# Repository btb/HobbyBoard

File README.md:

# HobbyBoard

## Reproduction of the original Apple Hobby/Prototyping Board

## Miniaturized version

Download gerber files at https://github.com/btb/HobbyBoard/releases

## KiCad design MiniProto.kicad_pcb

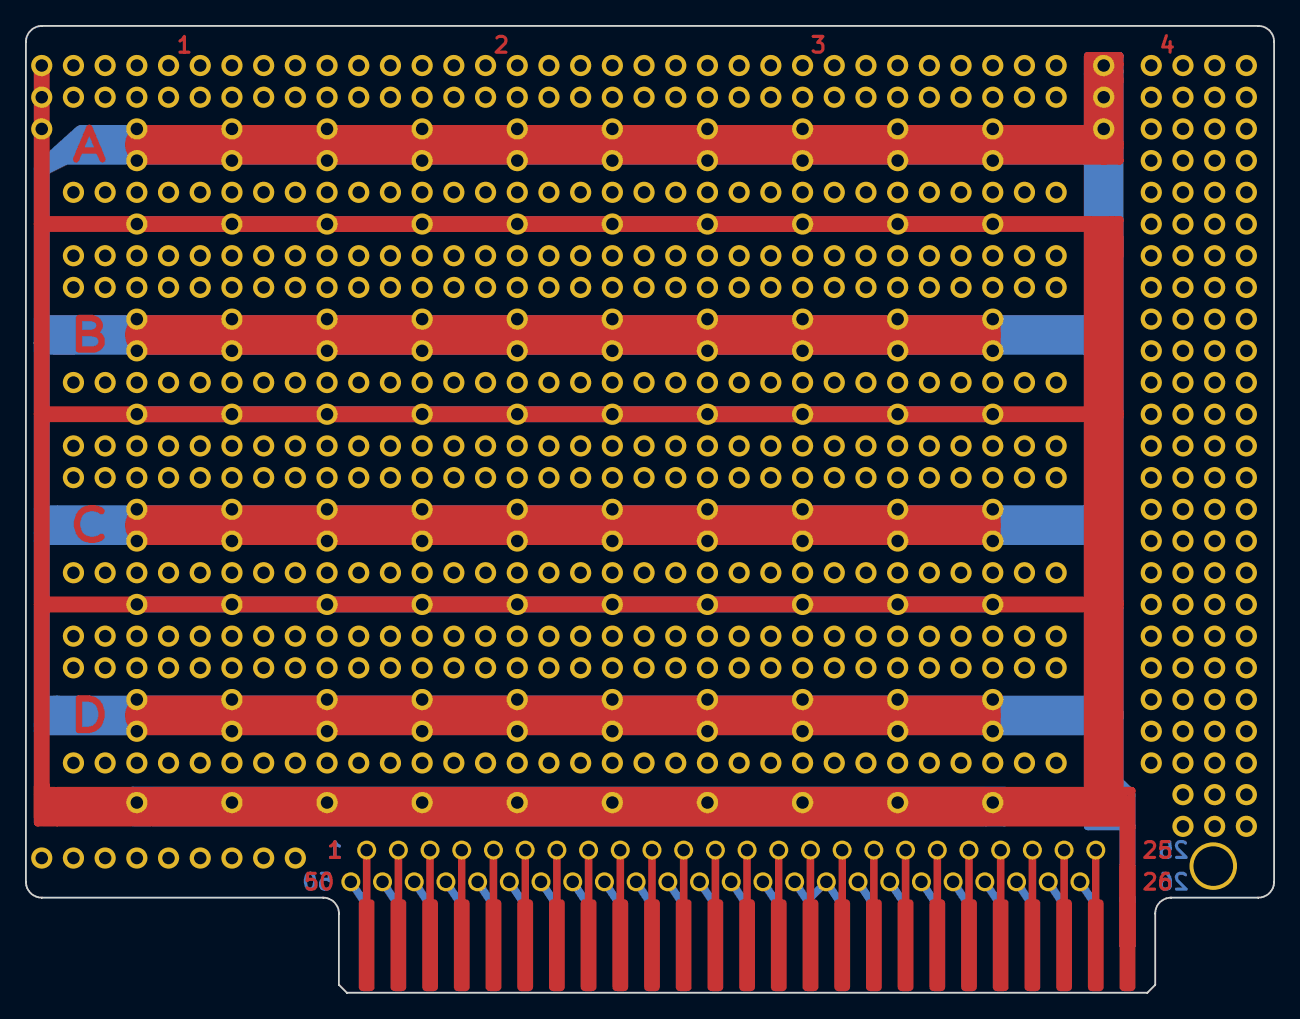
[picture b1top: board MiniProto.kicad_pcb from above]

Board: 2 copper layers, 100.0 x 77.5 mm, 4 parts (0 on the bottom side), 16 nets.

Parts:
H2: .125_Mounting_Hole; PTH_.125_ID
J1: Apple II Expansion Bus; Apple II Expansion Edge Connector
J2: Back Side; PinHeader_1x24_P2.54mm_Vertical
J3: Front Side; PinHeader_1x24_P2.54mm_Vertical

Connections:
unnamed: J1.1 (~IO_SELECT), J3.1
unnamed: J1.19 (N.C.), J3.19
unnamed: J1.20 (~I/O_STROBE), J3.20
unnamed: J1.21 (RDY), J3.21
unnamed: J1.22 (~DMA), J3.22
unnamed: J1.29 (~NMI), J2.3
unnamed: J1.30 (~IRQ), J2.4
unnamed: J1.31 (~RES), J2.5
unnamed: J1.33 (-12V), J2.7
unnamed: J1.34 (-5V), J2.8
unnamed: J1.35 (N.C.), J2.9
unnamed: J1.36 (7M), J2.10
unnamed: J1.37 (Q3), J2.11
unnamed: J1.38 (PHI1), J2.12
unnamed: J1.39 (USER1), J2.13
unnamed: J1.50 (-12V), J2.24

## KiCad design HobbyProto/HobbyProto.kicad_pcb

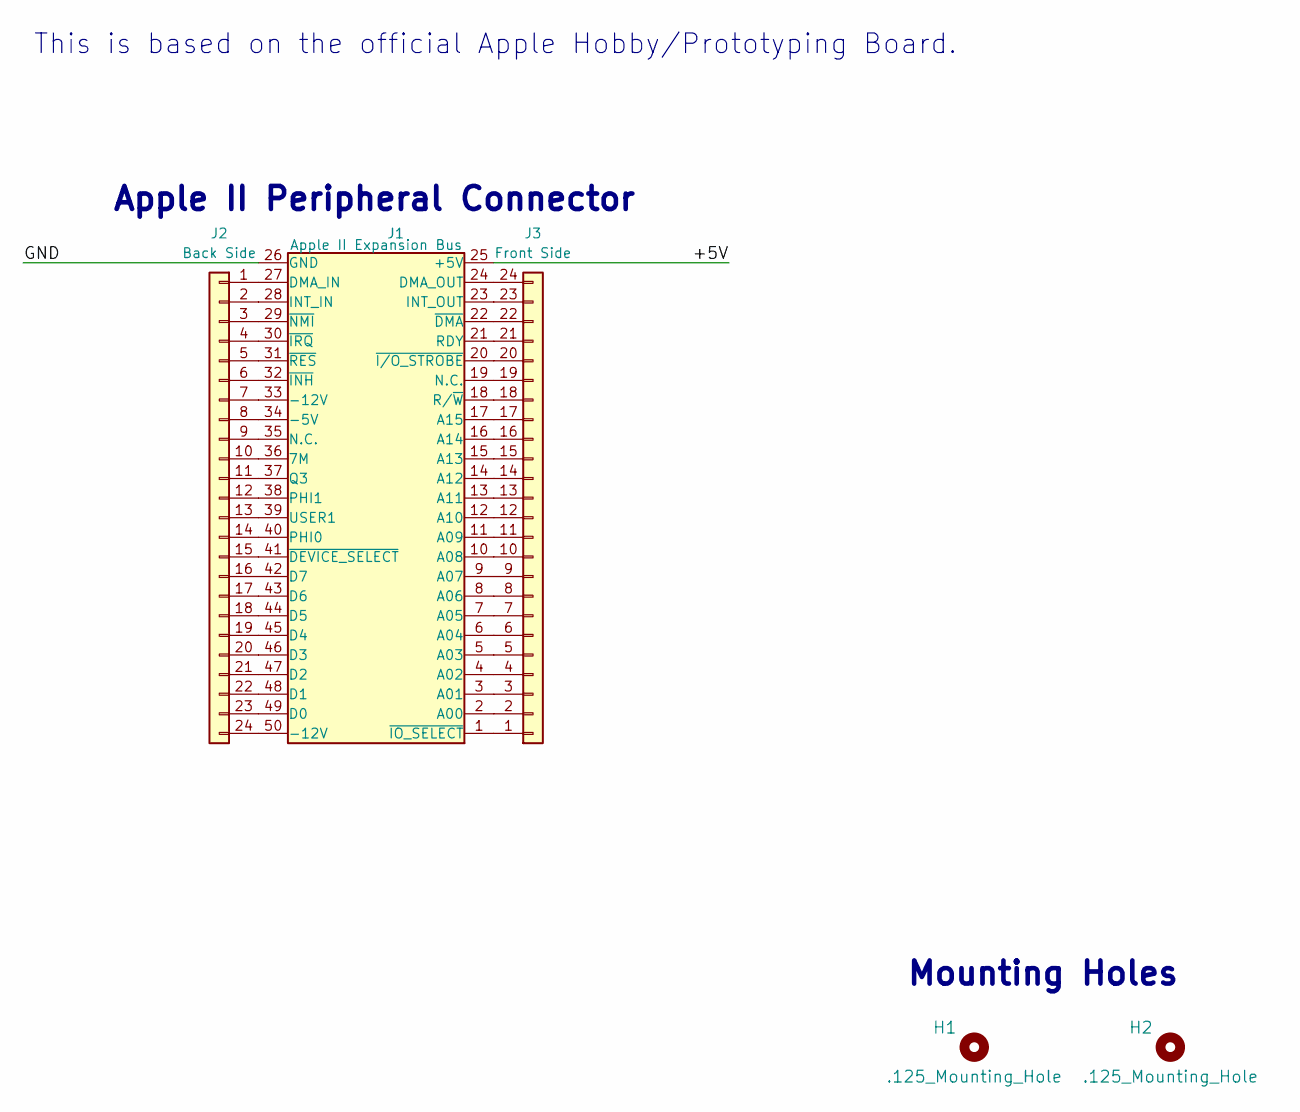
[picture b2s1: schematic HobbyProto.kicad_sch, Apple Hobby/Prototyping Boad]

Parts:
H1: .125_Mounting_Hole; NPTH_3mm_ID
H2: .125_Mounting_Hole; PTH_.125_ID
J1: Apple II Expansion Bus; Apple II Expansion Edge Connector
J2: Back Side; PinHeader_1x24_P2.54mm_Vertical
J3: Front Side; PinHeader_1x24_P2.54mm_Vertical

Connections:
/+5V: J1.25 (+5V)
/GND: J1.26 (GND)
unnamed: J1.1 (~IO_SELECT), J3.1
unnamed: J1.2 (A00), J3.2
unnamed: J1.3 (A01), J3.3
unnamed: J1.4 (A02), J3.4
unnamed: J1.5 (A03), J3.5
unnamed: J1.6 (A04), J3.6
unnamed: J1.7 (A05), J3.7
unnamed: J1.8 (A06), J3.8
unnamed: J1.9 (A07), J3.9
unnamed: J1.10 (A08), J3.10
unnamed: J1.11 (A09), J3.11
unnamed: J1.12 (A10), J3.12
unnamed: J1.13 (A11), J3.13
unnamed: J1.14 (A12), J3.14
unnamed: J1.15 (A13), J3.15
unnamed: J1.16 (A14), J3.16
unnamed: J1.17 (A15), J3.17
unnamed: J1.18 (R/~W), J3.18
unnamed: J1.19 (N.C.), J3.19
unnamed: J1.20 (~I/O_STROBE), J3.20
unnamed: J1.21 (RDY), J3.21
unnamed: J1.22 (~DMA), J3.22
unnamed: J1.23 (INT_OUT), J3.23
unnamed: J1.24 (DMA_OUT), J3.24
unnamed: J1.27 (DMA_IN), J2.1
unnamed: J1.28 (INT_IN), J2.2
unnamed: J1.29 (~NMI), J2.3
unnamed: J1.30 (~IRQ), J2.4
unnamed: J1.31 (~RES), J2.5
unnamed: J1.32 (~INH), J2.6
unnamed: J1.33 (-12V), J2.7
unnamed: J1.34 (-5V), J2.8
unnamed: J1.35 (N.C.), J2.9
unnamed: J1.36 (7M), J2.10
unnamed: J1.37 (Q3), J2.11
unnamed: J1.38 (PHI1), J2.12
unnamed: J1.39 (USER1), J2.13
unnamed: J1.40 (PHI0), J2.14
unnamed: J1.41 (~DEVICE_SELECT), J2.15
unnamed: J1.42 (D7), J2.16
unnamed: J1.43 (D6), J2.17
unnamed: J1.44 (D5), J2.18
unnamed: J1.45 (D4), J2.19
unnamed: J1.46 (D3), J2.20
unnamed: J1.47 (D2), J2.21
unnamed: J1.48 (D1), J2.22
unnamed: J1.49 (D0), J2.23
unnamed: J1.50 (-12V), J2.24

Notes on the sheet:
This is based on the official Apple Hobby/Prototyping Board.
Apple II Peripheral Connector
Mounting Holes

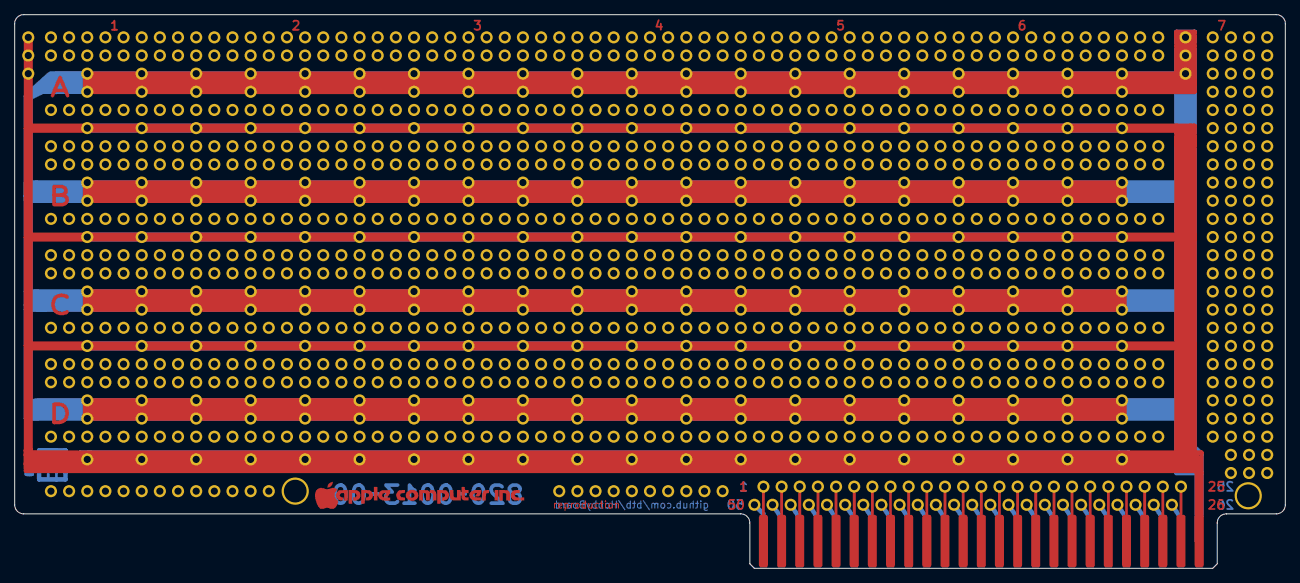
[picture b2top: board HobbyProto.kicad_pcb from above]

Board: 2 copper layers, 177.8 x 77.5 mm, 5 parts (0 on the bottom side), 48 nets.

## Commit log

2024-02-28 add kicad files
2024-02-28 move
2024-02-28 add Mini Proto
2024-02-28 add renders
2024-03-01 add gerbers
2024-03-01 move again
2024-03-01 readd gerbers
2024-03-01 fix readme
